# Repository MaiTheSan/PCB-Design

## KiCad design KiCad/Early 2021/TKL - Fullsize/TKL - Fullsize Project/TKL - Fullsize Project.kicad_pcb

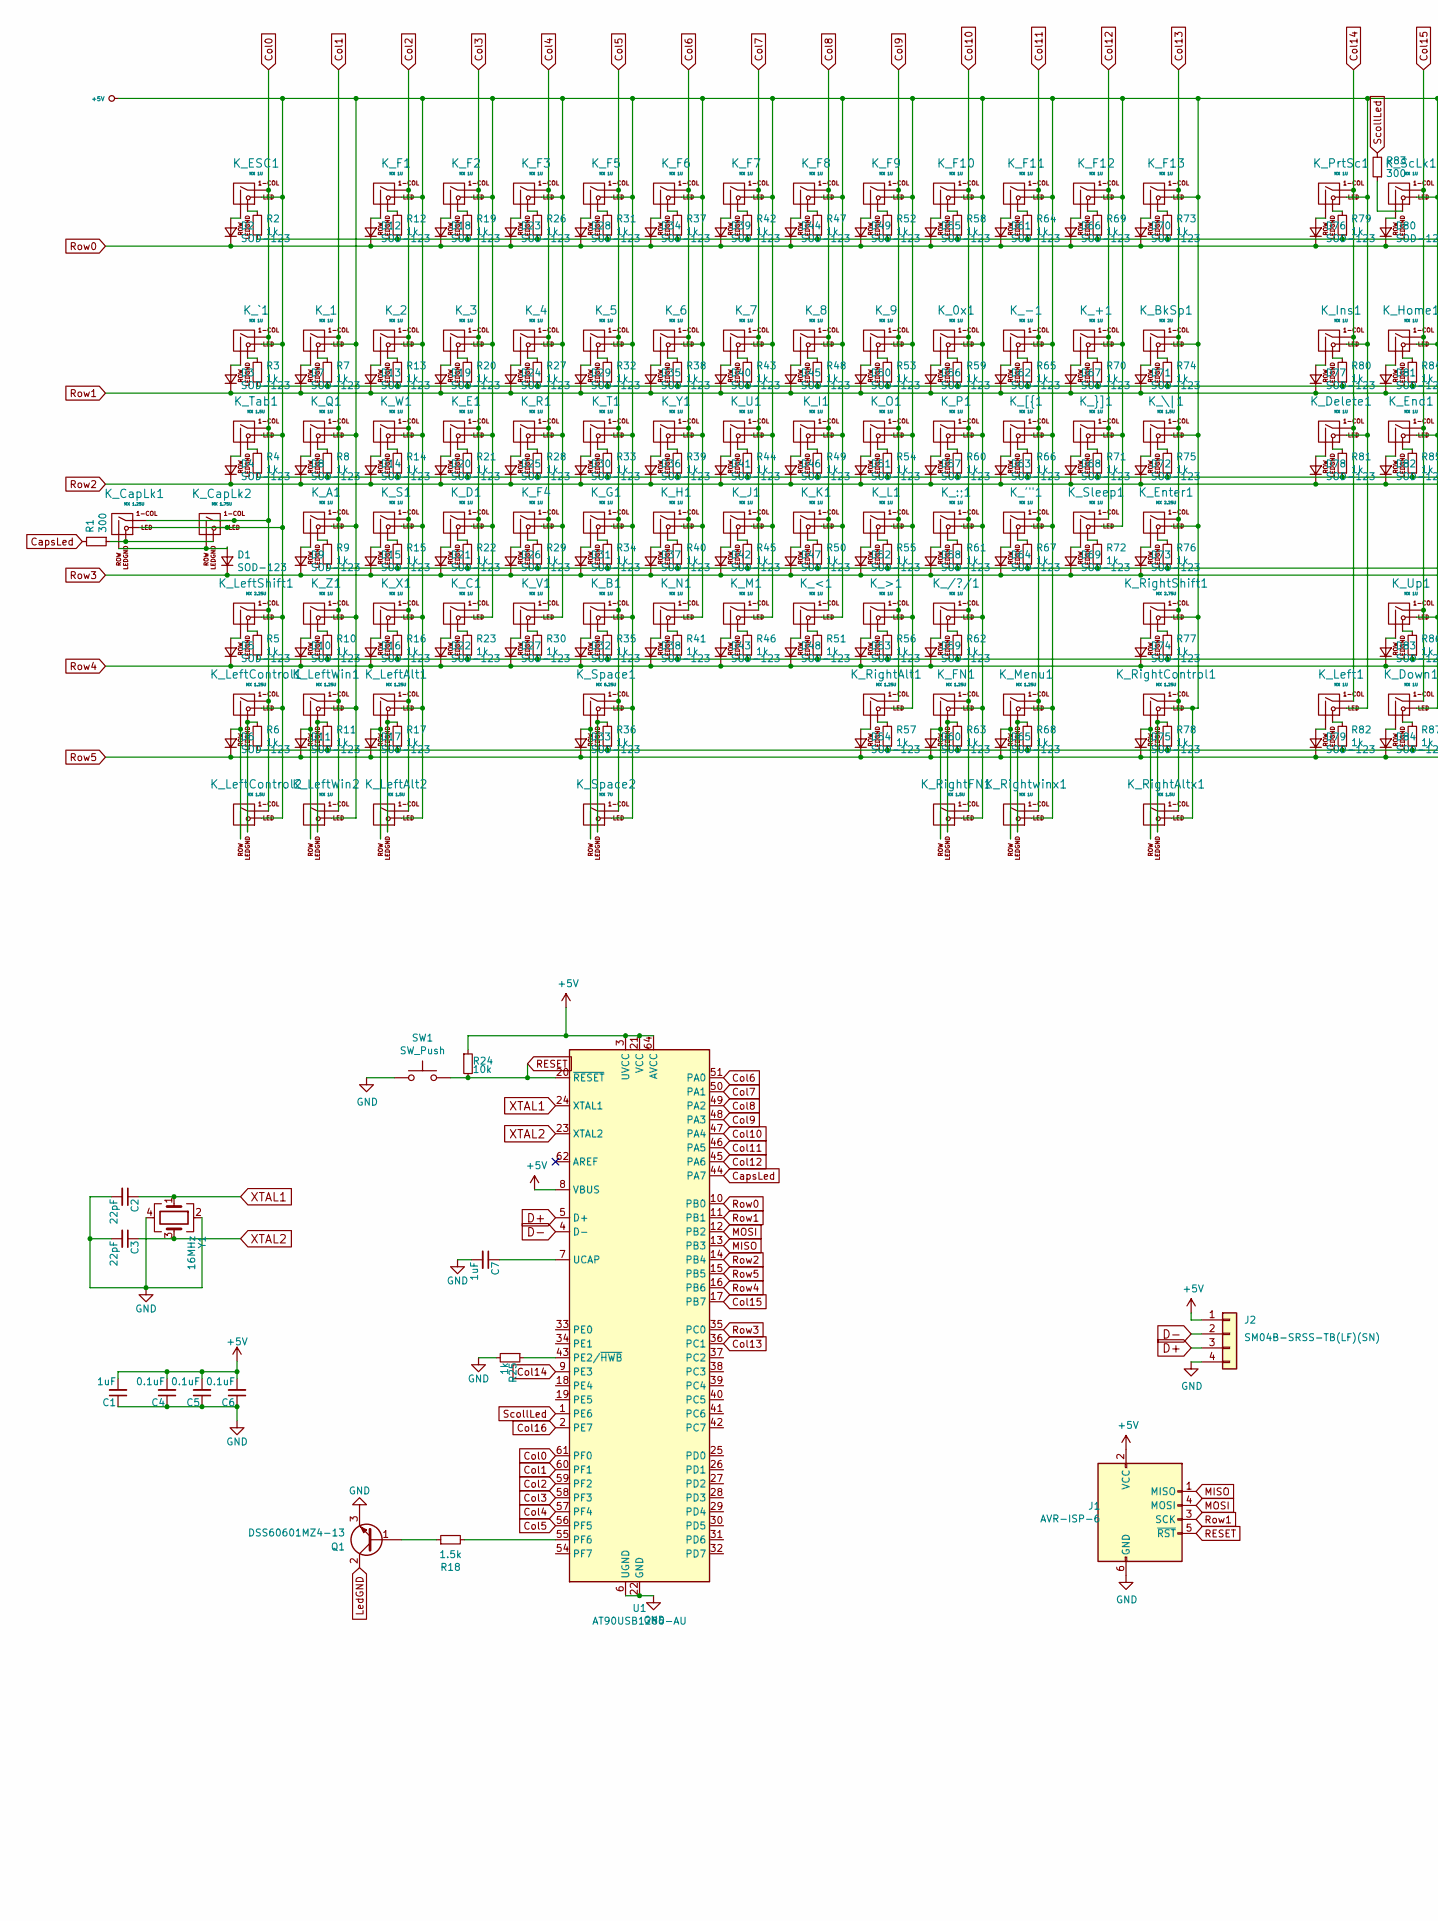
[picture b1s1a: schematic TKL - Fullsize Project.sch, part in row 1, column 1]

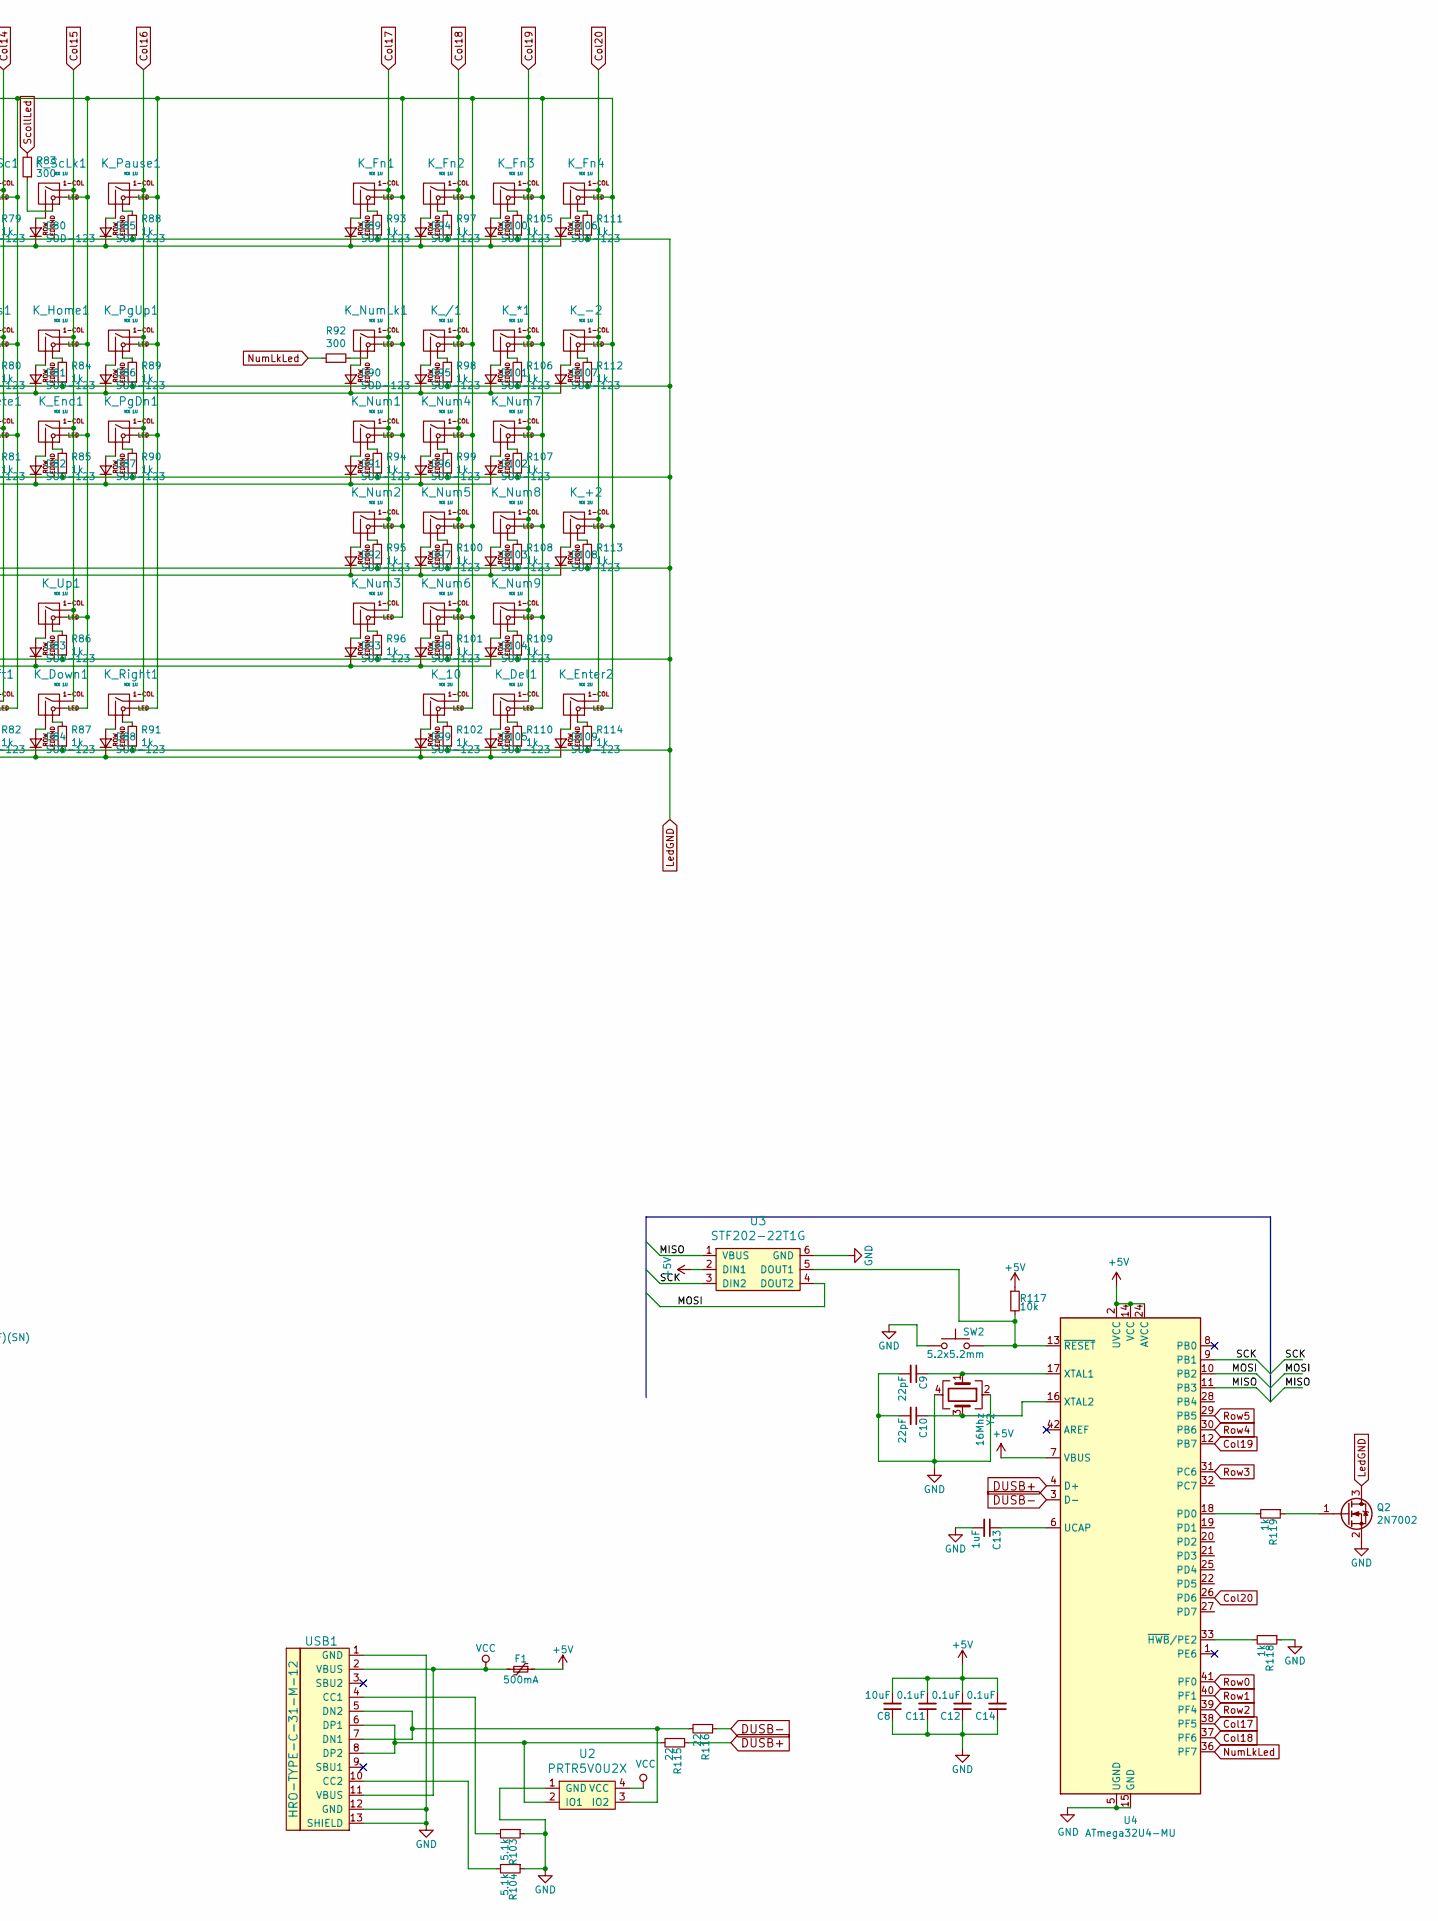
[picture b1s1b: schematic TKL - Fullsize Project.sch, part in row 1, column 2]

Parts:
C1, C7, C13: 1uF; C_0603
C2, C3, C9, C10: 22pF; C_0603
C4, C5, C6, C11, C12, C14: 0.1uF; C_0603
C8: 10uF; C_0603
D1, D2, D3, D4, D5, D6, D7, D8, D9, D10, D11, D12, D13, D14, D15, D16, D17, D18, D19, D20, D21, D22, D23, D24, D25, D26, D27, D28, D29, D30, D31, D32, D33, D34, D35, D36, D37, D38, D39, D40, D41, D42, D43, D44, D45, D46, D47, D48, D49, D50, D51, D52, D53, D54, D55, D56, D57, D58, D59, D60, D61, D62, D63, D64, D65, D66, D67, D68, D69, D70, D71, D72, D73, D74, D75, D76, D77, D78, D79, D80, D81, D82, D83, D84, D85, D86, D87, D88, D89, D90, D91, D92, D93, D94, D95, D96, D97, D98, D99, D100, D101, D102, D103, D104, D105, D106, D107, D108, D109: SOD-123; D_SOD-123-Pretty
F1: 500mA; Fuse_SMD1206_Reflow
J1: AVR-ISP-6; Reset_Pretty-Mask
J2: SM04B-SRSS-TB(LF)(SN); JST-SR-4; Manufacturer Part No SM04B-SRSS-TB(LF)(SN); LCSC Part No C160404
K_0x1, K_1, K_2, K_3, K_4, K_5, K_6, K_7, K_8, K_9: MX 1U; MXOnly-1U
K_10: MX 2U; MXOnly-2U-FLIPPED
K_'"1: MX 1U; MXOnly-1U
K_*1: MX 1U; MXOnly-1U
K_+1: MX 1U; MXOnly-1U
K_+2: MX 2U; MXOnly-2U
K_-1, K_-2: MX 1U; MXOnly-1U
K_/1: MX 1U; MXOnly-1U
K_/?/1: MX 1U; MXOnly-1U
K_:;1: MX 1U; MXOnly-1U
K_<1: MX 1U; MXOnly-1U
K_>1: MX 1U; MXOnly-1U
K_A1: MX 1U; MXOnly-1U
K_B1: MX 1U; MXOnly-1U
K_BkSp1: MX 2U; MXOnly-2U-ReversedStabilizers
K_C1: MX 1U; MXOnly-1U
K_CapLk1: MX 1.25U; MXOnly-1.25U
K_CapLk2: MX 1.75U; MXOnly-1.75U-FLIPPED
K_D1: MX 1U; MXOnly-1U
K_Del1: MX 1U; MXOnly-1U-FLIPPED
K_Delete1: MX 1U; MXOnly-1U
K_Down1: MX 1U; MXOnly-1U
K_E1: MX 1U; MXOnly-1U
K_ESC1: MX 1U; MXOnly-1U
K_End1: MX 1U; MXOnly-1U
K_Enter1: MX 2.25U; MXOnly-2.25U
K_Enter2: MX 2U; MXOnly-2U
K_F1, K_F2, K_F3, K_F4, K_F5, K_F6, K_F7, K_F8, K_F9, K_F10, K_F11, K_F12, K_F13: MX 1U; MXOnly-1U
K_FN1: MX 1.25U; MXOnly-1.25U-FLIPPED
K_Fn1, K_Fn3: MX 1U; MXOnly-1U-FLIPPED
K_Fn2, K_Fn4: MX 1U; MXOnly-1U
K_G1: MX 1U; MXOnly-1U
K_H1: MX 1U; MXOnly-1U
K_Home1: MX 1U; MXOnly-1U
K_I1: MX 1U; MXOnly-1U
K_Ins1: MX 1U; MXOnly-1U
K_J1: MX 1U; MXOnly-1U
K_K1: MX 1U; MXOnly-1U
K_L1: MX 1U; MXOnly-1U
K_Left1: MX 1U; MXOnly-1U
K_LeftAlt1: MX 1.25U; MXOnly-1.25U
K_LeftAlt2: MX 1.5U; MXOnly-1.5U-FLIPPED
K_LeftControl1: MX 1.25U; MXOnly-1.25U
K_LeftControl2: MX 1.5U; MXOnly-1.5U-FLIPPED
K_LeftShift1: MX 2.25U; MXOnly-2.25U
K_LeftWin1: MX 1.25U; MXOnly-1.25U
K_LeftWin2: MX 1U; MXOnly-1U-FLIPPED
K_M1: MX 1U; MXOnly-1U
K_Menu1: MX 1.25U; MXOnly-1.25U-FLIPPED
K_N1: MX 1U; MXOnly-1U
K_Num1, K_Num2, K_Num3, K_Num7, K_Num8, K_Num9: MX 1U; MXOnly-1U-FLIPPED
K_Num4, K_Num5, K_Num6: MX 1U; MXOnly-1U
K_NumLk1: MX 1U; MXOnly-1U-FLIPPED
K_O1: MX 1U; MXOnly-1U
K_P1: MX 1U; MXOnly-1U
K_Pause1: MX 1U; MXOnly-1U
K_PgDn1: MX 1U; MXOnly-1U
K_PgUp1: MX 1U; MXOnly-1U
K_PrtSc1: MX 1U; MXOnly-1U
K_Q1: MX 1U; MXOnly-1U
K_R1: MX 1U; MXOnly-1U
K_Right1: MX 1U; MXOnly-1U
K_RightAlt1: MX 1.25U; MXOnly-1.25U
K_RightAltx1: MX 1.5U; MXOnly-1.5U
K_RightControl1: MX 1.25U; MXOnly-1.25U-FLIPPED
K_RightFN1: MX 1.5U; MXOnly-1.5U
K_RightShift1: MX 2.75U; MXOnly-2.75U
K_Rightwinx1: MX 1U; MXOnly-1U
K_S1: MX 1U; MXOnly-1U
K_ScLk1: MX 1U; MXOnly-1U
K_Sleep1: MX 1U; MXOnly-1U
K_Space1: MX 6.25U; MXOnly-6.25U-FLIPPED
K_Space2: MX 7U; MXOnly-7U
K_T1: MX 1U; MXOnly-1U
K_Tab1: MX 1.5U; MXOnly-1.5U
K_U1: MX 1U; MXOnly-1U
K_Up1: MX 1U; MXOnly-1U
K_V1: MX 1U; MXOnly-1U
K_W1: MX 1U; MXOnly-1U
K_X1: MX 1U; MXOnly-1U
K_Y1: MX 1U; MXOnly-1U
K_Z1: MX 1U; MXOnly-1U
K_[{1: MX 1U; MXOnly-1U
K_\|1: MX 1.5U; MXOnly-1.5U
K_`1: MX 1U; MXOnly-1U
K_}]1: MX 1U; MXOnly-1U
Q1: DSS60601MZ4-13; SOT-223-3_TabPin2
Q2: 2N7002; SOT-23
R1, R83, R92: 300; R_0805
R2, R3, R4, R5, R6, R7, R8, R9, R10, R11, R12, R13, R14, R15, R16, R17, R19, R20, R21, R22, R23, R25, R26, R27, R28, R29, R30, R31, R32, R33, R34, R35, R36, R37, R38, R39, R40, R41, R42, R43, R44, R45, R46, R47, R48, R49, R50, R51, R52, R53, R54, R55, R56, R57, R58, R59, R60, R61, R62, R63, R64, R65, R66, R67, R68, R69, R70, R71, R72, R73, R74, R75, R76, R77, R78, R79, R80, R81, R82, R84, R85, R86, R87, R88, R89, R90, R91, R93, R94, R95, R96, R97, R98, R99, R100, R101, R102, R105, R106, R107, R108, R109, R110, R111, R112, R113, R114, R118, R119: 1k; R_0805
R18: 1.5k; R_0805
R24, R117: 10k; R_0805
R103, R104: 5.1k; R_0805
R115, R116: 22; R_0805
SW1: SW_Push; SKQG-1155865
SW2: 5.2x5.2mm; SKQG-1155865
U1: AT90USB1286-AU; TQFP-64_14x14mm_P0.8mm
U2: PRTR5V0U2X; SOT143B
U3: STF202-22T1G; Reset_Pretty-Mask
U4: ATmega32U4-MU; QFN-44-1EP_7x7mm_P0.5mm_EP5.2x5.2mm
USB1: HRO-TYPE-C-31-M-12; HRO-TYPE-C-31-M-12-Assembly
Y1: 16MHz; Crystal_SMD_3225-4Pin_3.2x2.5mm
Y2: 16Mhz; Crystal_SMD_3225-4Pin_3.2x2.5mm

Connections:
+5V: C1.2, C4.2, C5.2, C6.2, C8.2, C11.2, C12.2, C14.2, F1.1, J1.2 (VCC), J2.1, K_0x1.3 (LED), K_1.3 (LED), K_2.3 (LED), K_3.3 (LED), K_4.3 (LED), K_5.3 (LED), K_6.3 (LED), K_7.3 (LED), K_8.3 (LED), K_9.3 (LED), K_10.3 (LED), K_'"1.3 (LED), K_*1.3 (LED), K_+1.3 (LED), K_+2.3 (LED), K_-1.3 (LED), K_-2.3 (LED), K_/1.3 (LED), K_/?/1.3 (LED), K_:;1.3 (LED), K_<1.3 (LED), K_>1.3 (LED), K_A1.3 (LED), K_B1.3 (LED), K_BkSp1.3 (LED), K_C1.3 (LED), K_CapLk1.3 (LED), K_CapLk2.3 (LED), K_D1.3 (LED), K_Del1.3 (LED), K_Delete1.3 (LED), K_Down1.3 (LED), K_E1.3 (LED), K_ESC1.3 (LED), K_End1.3 (LED), K_Enter1.3 (LED), K_Enter2.3 (LED), K_F1.3 (LED), K_F2.3 (LED), K_F3.3 (LED), K_F4.3 (LED), K_F5.3 (LED), K_F6.3 (LED), K_F7.3 (LED), K_F8.3 (LED), K_F9.3 (LED), K_F10.3 (LED), K_F11.3 (LED), K_F12.3 (LED), K_F13.3 (LED), K_FN1.3 (LED), K_Fn1.3 (LED), K_Fn2.3 (LED), K_Fn3.3 (LED), K_Fn4.3 (LED), K_G1.3 (LED), K_H1.3 (LED), K_Home1.3 (LED), K_I1.3 (LED), K_Ins1.3 (LED), K_J1.3 (LED), K_K1.3 (LED), K_L1.3 (LED), K_Left1.3 (LED), K_LeftAlt1.3 (LED), K_LeftAlt2.3 (LED), K_LeftControl1.3 (LED), K_LeftControl2.3 (LED), K_LeftShift1.3 (LED), K_LeftWin1.3 (LED), K_LeftWin2.3 (LED), K_M1.3 (LED), K_Menu1.3 (LED), K_N1.3 (LED), K_Num1.3 (LED), K_Num2.3 (LED), K_Num3.3 (LED), K_Num4.3 (LED), K_Num5.3 (LED), K_Num6.3 (LED), K_Num7.3 (LED), K_Num8.3 (LED), K_Num9.3 (LED), K_NumLk1.3 (LED), K_O1.3 (LED), K_P1.3 (LED), K_Pause1.3 (LED), K_PgDn1.3 (LED), K_PgUp1.3 (LED), K_PrtSc1.3 (LED), K_Q1.3 (LED), K_R1.3 (LED), K_Right1.3 (LED), K_RightAlt1.3 (LED), K_RightAltx1.3 (LED), K_RightControl1.3 (LED), K_RightFN1.3 (LED), K_RightShift1.3 (LED), K_Rightwinx1.3 (LED), K_S1.3 (LED), K_ScLk1.3 (LED), K_Sleep1.3 (LED), K_Space1.3 (LED), K_Space2.3 (LED), K_T1.3 (LED), K_Tab1.3 (LED), K_U1.3 (LED), K_Up1.3 (LED), K_V1.3 (LED), K_W1.3 (LED), K_X1.3 (LED), K_Y1.3 (LED), K_Z1.3 (LED), K_[{1.3 (LED), K_\|1.3 (LED), K_`1.3 (LED), K_}]1.3 (LED), R24.1, R117.1, U1.3 (UVCC), U1.8 (VBUS), U1.21 (VCC), U1.52 (VCC), U1.64 (AVCC), U3.2 (DIN1), U4.2 (UVCC), U4.7 (VBUS), U4.14 (VCC), U4.24 (AVCC), U4.34 (VCC), U4.44 (AVCC)
/SCK: U3.3 (DIN2), U4.9 (PB1)
CapsLed: R1.2, U1.44 (PA7)
Col0: K_CapLk1.1 (COL), K_CapLk2.1 (COL), K_ESC1.1 (COL), K_LeftControl1.1 (COL), K_LeftControl2.1 (COL), K_LeftShift1.1 (COL), K_Tab1.1 (COL), K_`1.1 (COL), U1.61 (PF0)
Col1: K_1.1 (COL), K_A1.1 (COL), K_LeftWin1.1 (COL), K_LeftWin2.1 (COL), K_Q1.1 (COL), K_Z1.1 (COL), U1.60 (PF1)
Col2: K_2.1 (COL), K_F1.1 (COL), K_LeftAlt1.1 (COL), K_LeftAlt2.1 (COL), K_S1.1 (COL), K_W1.1 (COL), K_X1.1 (COL), U1.59 (PF2)
Col3: K_3.1 (COL), K_C1.1 (COL), K_D1.1 (COL), K_E1.1 (COL), K_F2.1 (COL), U1.58 (PF3)
Col4: K_4.1 (COL), K_F3.1 (COL), K_F4.1 (COL), K_R1.1 (COL), K_V1.1 (COL), U1.57 (PF4)
Col5: K_5.1 (COL), K_B1.1 (COL), K_F5.1 (COL), K_G1.1 (COL), K_Space1.1 (COL), K_Space2.1 (COL), K_T1.1 (COL), U1.56 (PF5)
Col6: K_6.1 (COL), K_F6.1 (COL), K_H1.1 (COL), K_N1.1 (COL), K_Y1.1 (COL), U1.51 (PA0)
Col7: K_7.1 (COL), K_F7.1 (COL), K_J1.1 (COL), K_M1.1 (COL), K_U1.1 (COL), U1.50 (PA1)
Col8: K_8.1 (COL), K_<1.1 (COL), K_F8.1 (COL), K_I1.1 (COL), K_K1.1 (COL), U1.49 (PA2)
Col9: K_9.1 (COL), K_>1.1 (COL), K_F9.1 (COL), K_L1.1 (COL), K_O1.1 (COL), K_RightAlt1.1 (COL), U1.48 (PA3)
Col10: K_0x1.1 (COL), K_/?/1.1 (COL), K_:;1.1 (COL), K_F10.1 (COL), K_FN1.1 (COL), K_P1.1 (COL), K_RightFN1.1 (COL), U1.47 (PA4)
Col11: K_'"1.1 (COL), K_-1.1 (COL), K_F11.1 (COL), K_Menu1.1 (COL), K_Rightwinx1.1 (COL), K_[{1.1 (COL), U1.46 (PA5)
Col12: K_+1.1 (COL), K_F12.1 (COL), K_Sleep1.1 (COL), K_}]1.1 (COL), U1.45 (PA6)
Col13: K_BkSp1.1 (COL), K_Enter1.1 (COL), K_F13.1 (COL), K_RightAltx1.1 (COL), K_RightControl1.1 (COL), K_RightShift1.1 (COL), K_\|1.1 (COL), U1.36 (PC1)
Col14: K_Delete1.1 (COL), K_Ins1.1 (COL), K_Left1.1 (COL), K_PrtSc1.1 (COL), U1.9 (PE3)
Col15: K_Down1.1 (COL), K_End1.1 (COL), K_Home1.1 (COL), K_ScLk1.1 (COL), K_Up1.1 (COL), U1.17 (PB7)
Col16: K_Pause1.1 (COL), K_PgDn1.1 (COL), K_PgUp1.1 (COL), K_Right1.1 (COL), U1.2 (PE7)
Col17: K_Fn1.1 (COL), K_Num1.1 (COL), K_Num2.1 (COL), K_Num3.1 (COL), K_NumLk1.1 (COL), U4.38 (PF5)
Col18: K_10.1 (COL), K_/1.1 (COL), K_Fn2.1 (COL), K_Num4.1 (COL), K_Num5.1 (COL), K_Num6.1 (COL), U4.37 (PF6)
Col19: K_*1.1 (COL), K_Del1.1 (COL), K_Fn3.1 (COL), K_Num7.1 (COL), K_Num8.1 (COL), K_Num9.1 (COL), U4.12 (PB7)
Col20: K_+2.1 (COL), K_-2.1 (COL), K_Enter2.1 (COL), K_Fn4.1 (COL), U4.26 (PD6)
D+: J2.3, U1.5 (D+)
D-: J2.2, U1.4 (D-)
DUSB+: R115.1, U4.4 (D+)
DUSB-: R116.1, U4.3 (D-)
GND: C1.1, C2.2, C3.2, C4.1, C5.1, C6.1, C7.2, C8.1, C9.2, C10.2, C11.1, C12.1, C13.2, C14.1, J1.6 (GND), J2.4, Q1.3 (E), Q2.2 (S), R25.2, R103.1, R104.1, R118.1, SW1.1, SW2.1, U1.6 (UGND), U1.22 (GND), U1.53 (GND), U1.63 (GND), U2.1 (GND), U3.6 (GND), U4.5 (UGND), U4.15 (GND), U4.23 (GND), U4.35 (GND), U4.43 (GND), U4.45 (GND), USB1.1 (GND), USB1.12 (GND), USB1.13 (SHIELD), Y1.2, Y1.4, Y2.2, Y2.4
LedGND: Q1.2 (C), Q2.3 (D), R2.1, R3.1, R4.1, R5.1, R6.1, R7.1, R8.1, R9.1, R10.1, R11.1, R12.1, R13.1, R14.1, R15.1, R16.1, R17.1, R19.1, R20.1, R21.1, R22.1, R23.1, R26.1, R27.1, R28.1, R29.1, R30.1, R31.1, R32.1, R33.1, R34.1, R35.1, R36.1, R37.1, R38.1, R39.1, R40.1, R41.1, R42.1, R43.1, R44.1, R45.1, R46.1, R47.1, R48.1, R49.1, R50.1, R51.1, R52.1, R53.1, R54.1, R55.1, R56.1, R57.1, R58.1, R59.1, R60.1, R61.1, R62.1, R63.1, R64.1, R65.1, R66.1, R67.1, R68.1, R69.1, R70.1, R71.1, R72.1, R73.1, R74.1, R75.1, R76.1, R77.1, R78.1, R79.1, R80.1, R81.1, R82.1, R84.1, R85.1, R86.1, R87.1, R88.1, R89.1, R90.1, R91.1, R93.1, R94.1, R95.1, R96.1, R97.1, R98.1, R99.1, R100.1, R101.1, R102.1, R105.1, R106.1, R107.1, R108.1, R109.1, R110.1, R111.1, R112.1, R113.1, R114.1
MISO: J1.1 (MISO), U1.13 (PB3), U3.1 (VBUS), U4.11 (PB3)
MOSI: J1.4 (MOSI), U1.12 (PB2), U3.4 (DOUT2), U4.10 (PB2)
unnamed: C7.1, U1.7 (UCAP)
unnamed: C9.1, U4.17 (XTAL1), Y2.1
unnamed: C10.1, U4.16 (XTAL2), Y2.3
unnamed: C13.1, U4.6 (UCAP)
unnamed: D1.2 (A), K_CapLk1.2 (ROW), K_CapLk2.2 (ROW)
unnamed: D2.2 (A), K_ESC1.2 (ROW)
unnamed: D3.2 (A), K_`1.2 (ROW)
unnamed: D4.2 (A), K_Tab1.2 (ROW)
unnamed: D5.2 (A), K_LeftShift1.2 (ROW)
unnamed: D6.2 (A), K_LeftControl1.2 (ROW), K_LeftControl2.2 (ROW)
unnamed: D7.2 (A), K_1.2 (ROW)
unnamed: D8.2 (A), K_Q1.2 (ROW)
unnamed: D9.2 (A), K_A1.2 (ROW)
unnamed: D10.2 (A), K_Z1.2 (ROW)
unnamed: D11.2 (A), K_LeftWin1.2 (ROW), K_LeftWin2.2 (ROW)
unnamed: D12.2 (A), K_F1.2 (ROW)
unnamed: D13.2 (A), K_2.2 (ROW)
unnamed: D14.2 (A), K_W1.2 (ROW)
unnamed: D15.2 (A), K_S1.2 (ROW)
unnamed: D16.2 (A), K_X1.2 (ROW)
unnamed: D17.2 (A), K_LeftAlt1.2 (ROW), K_LeftAlt2.2 (ROW)
unnamed: D18.2 (A), K_F2.2 (ROW)
unnamed: D19.2 (A), K_3.2 (ROW)
unnamed: D20.2 (A), K_E1.2 (ROW)
unnamed: D21.2 (A), K_D1.2 (ROW)
unnamed: D22.2 (A), K_C1.2 (ROW)
unnamed: D23.2 (A), K_F3.2 (ROW)
unnamed: D24.2 (A), K_4.2 (ROW)
unnamed: D25.2 (A), K_R1.2 (ROW)
unnamed: D26.2 (A), K_F4.2 (ROW)
unnamed: D27.2 (A), K_V1.2 (ROW)
unnamed: D28.2 (A), K_F5.2 (ROW)
unnamed: D29.2 (A), K_5.2 (ROW)
unnamed: D30.2 (A), K_T1.2 (ROW)
unnamed: D31.2 (A), K_G1.2 (ROW)
unnamed: D32.2 (A), K_B1.2 (ROW)
unnamed: D33.2 (A), K_Space1.2 (ROW), K_Space2.2 (ROW)
unnamed: D34.2 (A), K_F6.2 (ROW)
unnamed: D35.2 (A), K_6.2 (ROW)
unnamed: D36.2 (A), K_Y1.2 (ROW)
unnamed: D37.2 (A), K_H1.2 (ROW)
unnamed: D38.2 (A), K_N1.2 (ROW)
unnamed: D39.2 (A), K_F7.2 (ROW)
unnamed: D40.2 (A), K_7.2 (ROW)
unnamed: D41.2 (A), K_U1.2 (ROW)
unnamed: D42.2 (A), K_J1.2 (ROW)
unnamed: D43.2 (A), K_M1.2 (ROW)
unnamed: D44.2 (A), K_F8.2 (ROW)
unnamed: D45.2 (A), K_8.2 (ROW)
unnamed: D46.2 (A), K_I1.2 (ROW)
unnamed: D47.2 (A), K_K1.2 (ROW)
unnamed: D48.2 (A), K_<1.2 (ROW)
unnamed: D49.2 (A), K_F9.2 (ROW)
unnamed: D50.2 (A), K_9.2 (ROW)
unnamed: D51.2 (A), K_O1.2 (ROW)
unnamed: D52.2 (A), K_L1.2 (ROW)
unnamed: D53.2 (A), K_>1.2 (ROW)
unnamed: D54.2 (A), K_RightAlt1.2 (ROW)
unnamed: D55.2 (A), K_F10.2 (ROW)
unnamed: D56.2 (A), K_0x1.2 (ROW)
unnamed: D57.2 (A), K_P1.2 (ROW)
unnamed: D58.2 (A), K_:;1.2 (ROW)
unnamed: D59.2 (A), K_/?/1.2 (ROW)
unnamed: D60.2 (A), K_FN1.2 (ROW), K_RightFN1.2 (ROW)
unnamed: D61.2 (A), K_F11.2 (ROW)
unnamed: D62.2 (A), K_-1.2 (ROW)
unnamed: D63.2 (A), K_[{1.2 (ROW)
unnamed: D64.2 (A), K_'"1.2 (ROW)
unnamed: D65.2 (A), K_Menu1.2 (ROW), K_Rightwinx1.2 (ROW)
unnamed: D66.2 (A), K_F12.2 (ROW)
unnamed: D67.2 (A), K_+1.2 (ROW)
unnamed: D68.2 (A), K_}]1.2 (ROW)
unnamed: D69.2 (A), K_Sleep1.2 (ROW)
unnamed: D70.2 (A), K_F13.2 (ROW)
unnamed: D71.2 (A), K_BkSp1.2 (ROW)
unnamed: D72.2 (A), K_\|1.2 (ROW)
unnamed: D73.2 (A), K_Enter1.2 (ROW)
unnamed: D74.2 (A), K_RightShift1.2 (ROW)
unnamed: D75.2 (A), K_RightAltx1.2 (ROW), K_RightControl1.2 (ROW)
unnamed: D76.2 (A), K_PrtSc1.2 (ROW)
unnamed: D77.2 (A), K_Ins1.2 (ROW)
unnamed: D78.2 (A), K_Delete1.2 (ROW)
unnamed: D79.2 (A), K_Left1.2 (ROW)
unnamed: D80.2 (A), K_ScLk1.2 (ROW)
unnamed: D81.2 (A), K_Home1.2 (ROW)
unnamed: D82.2 (A), K_End1.2 (ROW)
unnamed: D83.2 (A), K_Up1.2 (ROW)
unnamed: D84.2 (A), K_Down1.2 (ROW)
unnamed: D85.2 (A), K_Pause1.2 (ROW)
unnamed: D86.2 (A), K_PgUp1.2 (ROW)
unnamed: D87.2 (A), K_PgDn1.2 (ROW)
unnamed: D88.2 (A), K_Right1.2 (ROW)
unnamed: D89.2 (A), K_Fn1.2 (ROW)
unnamed: D90.2 (A), K_NumLk1.2 (ROW)
unnamed: D91.2 (A), K_Num1.2 (ROW)
unnamed: D92.2 (A), K_Num2.2 (ROW)
unnamed: D93.2 (A), K_Num3.2 (ROW)
unnamed: D94.2 (A), K_Fn2.2 (ROW)
unnamed: D95.2 (A), K_/1.2 (ROW)
unnamed: D96.2 (A), K_Num4.2 (ROW)
unnamed: D97.2 (A), K_Num5.2 (ROW)
unnamed: D98.2 (A), K_Num6.2 (ROW)
unnamed: D99.2 (A), K_10.2 (ROW)
unnamed: D100.2 (A), K_Fn3.2 (ROW)
unnamed: D101.2 (A), K_*1.2 (ROW)
unnamed: D102.2 (A), K_Num7.2 (ROW)
unnamed: D103.2 (A), K_Num8.2 (ROW)
unnamed: D104.2 (A), K_Num9.2 (ROW)
unnamed: D105.2 (A), K_Del1.2 (ROW)
unnamed: D106.2 (A), K_Fn4.2 (ROW)
unnamed: D107.2 (A), K_-2.2 (ROW)
unnamed: D108.2 (A), K_+2.2 (ROW)
unnamed: D109.2 (A), K_Enter2.2 (ROW)
unnamed: K_0x1.4 (LEDGND), R59.2
unnamed: K_1.4 (LEDGND), R7.2
unnamed: K_2.4 (LEDGND), R13.2
unnamed: K_3.4 (LEDGND), R20.2
unnamed: K_4.4 (LEDGND), R27.2
unnamed: K_5.4 (LEDGND), R32.2
unnamed: K_6.4 (LEDGND), R38.2
unnamed: K_7.4 (LEDGND), R43.2
unnamed: K_8.4 (LEDGND), R48.2
unnamed: K_9.4 (LEDGND), R53.2
unnamed: K_10.4 (LEDGND), R102.2
unnamed: K_'"1.4 (LEDGND), R67.2
unnamed: K_*1.4 (LEDGND), R106.2
unnamed: K_+1.4 (LEDGND), R70.2
unnamed: K_+2.4 (LEDGND), R113.2
unnamed: K_-1.4 (LEDGND), R65.2
unnamed: K_-2.4 (LEDGND), R112.2
unnamed: K_/1.4 (LEDGND), R98.2
unnamed: K_/?/1.4 (LEDGND), R62.2
unnamed: K_:;1.4 (LEDGND), R61.2
unnamed: K_<1.4 (LEDGND), R51.2
unnamed: K_>1.4 (LEDGND), R56.2
unnamed: K_A1.4 (LEDGND), R9.2
unnamed: K_B1.4 (LEDGND), R35.2
unnamed: K_BkSp1.4 (LEDGND), R74.2
unnamed: K_C1.4 (LEDGND), R23.2
unnamed: K_CapLk1.4 (LEDGND), K_CapLk2.4 (LEDGND), R1.1
unnamed: K_D1.4 (LEDGND), R22.2
unnamed: K_Del1.4 (LEDGND), R110.2
unnamed: K_Delete1.4 (LEDGND), R81.2
unnamed: K_Down1.4 (LEDGND), R87.2
unnamed: K_E1.4 (LEDGND), R21.2
unnamed: K_ESC1.4 (LEDGND), R2.2
unnamed: K_End1.4 (LEDGND), R85.2
unnamed: K_Enter1.4 (LEDGND), R76.2
unnamed: K_Enter2.4 (LEDGND), R114.2
unnamed: K_F1.4 (LEDGND), R12.2
unnamed: K_F2.4 (LEDGND), R19.2
unnamed: K_F3.4 (LEDGND), R26.2
unnamed: K_F4.4 (LEDGND), R29.2
unnamed: K_F5.4 (LEDGND), R31.2
unnamed: K_F6.4 (LEDGND), R37.2
unnamed: K_F7.4 (LEDGND), R42.2
unnamed: K_F8.4 (LEDGND), R47.2
unnamed: K_F9.4 (LEDGND), R52.2
unnamed: K_F10.4 (LEDGND), R58.2
unnamed: K_F11.4 (LEDGND), R64.2
unnamed: K_F12.4 (LEDGND), R69.2
unnamed: K_F13.4 (LEDGND), R73.2
unnamed: K_FN1.4 (LEDGND), K_RightFN1.4 (LEDGND), R63.2
unnamed: K_Fn1.4 (LEDGND), R93.2
unnamed: K_Fn2.4 (LEDGND), R97.2
unnamed: K_Fn3.4 (LEDGND), R105.2
unnamed: K_Fn4.4 (LEDGND), R111.2
unnamed: K_G1.4 (LEDGND), R34.2
unnamed: K_H1.4 (LEDGND), R40.2
unnamed: K_Home1.4 (LEDGND), R84.2
unnamed: K_I1.4 (LEDGND), R49.2
unnamed: K_Ins1.4 (LEDGND), R80.2
unnamed: K_J1.4 (LEDGND), R45.2
unnamed: K_K1.4 (LEDGND), R50.2
unnamed: K_L1.4 (LEDGND), R55.2
unnamed: K_Left1.4 (LEDGND), R82.2
unnamed: K_LeftAlt1.4 (LEDGND), K_LeftAlt2.4 (LEDGND), R17.2
unnamed: K_LeftControl1.4 (LEDGND), K_LeftControl2.4 (LEDGND), R6.2
unnamed: K_LeftShift1.4 (LEDGND), R5.2
unnamed: K_LeftWin1.4 (LEDGND), K_LeftWin2.4 (LEDGND), R11.2
unnamed: K_M1.4 (LEDGND), R46.2
unnamed: K_Menu1.4 (LEDGND), K_Rightwinx1.4 (LEDGND), R68.2
unnamed: K_N1.4 (LEDGND), R41.2
unnamed: K_Num1.4 (LEDGND), R94.2
unnamed: K_Num2.4 (LEDGND), R95.2
unnamed: K_Num3.4 (LEDGND), R96.2
unnamed: K_Num4.4 (LEDGND), R99.2
unnamed: K_Num5.4 (LEDGND), R100.2
unnamed: K_Num6.4 (LEDGND), R101.2
unnamed: K_Num7.4 (LEDGND), R107.2
unnamed: K_Num8.4 (LEDGND), R108.2
unnamed: K_Num9.4 (LEDGND), R109.2
unnamed: K_NumLk1.4 (LEDGND), R92.2
unnamed: K_O1.4 (LEDGND), R54.2
unnamed: K_P1.4 (LEDGND), R60.2
unnamed: K_Pause1.4 (LEDGND), R88.2
unnamed: K_PgDn1.4 (LEDGND), R90.2
unnamed: K_PgUp1.4 (LEDGND), R89.2
unnamed: K_PrtSc1.4 (LEDGND), R79.2
unnamed: K_Q1.4 (LEDGND), R8.2
unnamed: K_R1.4 (LEDGND), R28.2
unnamed: K_Right1.4 (LEDGND), R91.2
unnamed: K_RightAlt1.4 (LEDGND), R57.2
unnamed: K_RightAltx1.4 (LEDGND), K_RightControl1.4 (LEDGND), R78.2
unnamed: K_RightShift1.4 (LEDGND), R77.2
unnamed: K_S1.4 (LEDGND), R15.2
unnamed: K_ScLk1.4 (LEDGND), R83.1
unnamed: K_Sleep1.4 (LEDGND), R72.2
unnamed: K_Space1.4 (LEDGND), K_Space2.4 (LEDGND), R36.2
unnamed: K_T1.4 (LEDGND), R33.2
unnamed: K_Tab1.4 (LEDGND), R4.2
unnamed: K_U1.4 (LEDGND), R44.2
unnamed: K_Up1.4 (LEDGND), R86.2
unnamed: K_V1.4 (LEDGND), R30.2
unnamed: K_W1.4 (LEDGND), R14.2
unnamed: K_X1.4 (LEDGND), R16.2
unnamed: K_Y1.4 (LEDGND), R39.2
unnamed: K_Z1.4 (LEDGND), R10.2
unnamed: K_[{1.4 (LEDGND), R66.2
unnamed: K_\|1.4 (LEDGND), R75.2
unnamed: K_`1.4 (LEDGND), R3.2
unnamed: K_}]1.4 (LEDGND), R71.2
unnamed: Q1.1 (B), R18.1
unnamed: Q2.1 (G), R119.1
unnamed: R18.2, U1.55 (PF6)
unnamed: R25.1, U1.43 (PE2/~HWB)
unnamed: R103.2, USB1.4 (CC1)
unnamed: R104.2, USB1.10 (CC2)
unnamed: R115.2, U2.2 (IO1), USB1.6 (DP1), USB1.8 (DP2)
unnamed: R116.2, U2.3 (IO2), USB1.5 (DN2), USB1.7 (DN1)
unnamed: R117.2, SW2.2, U3.5 (DOUT1), U4.13 (~RESET)
unnamed: R118.2, U4.33 (~HWB~/PE2)
unnamed: R119.2, U4.18 (PD0)
NumLkLed: R92.1, U4.36 (PF7)
RESET: J1.5 (~RST), R24.2, SW1.2, U1.20 (~RESET)
Row0: D2.1 (K), D12.1 (K), D18.1 (K), D23.1 (K), D28.1 (K), D34.1 (K), D39.1 (K), D44.1 (K), D49.1 (K), D55.1 (K), D61.1 (K), D66.1 (K), D70.1 (K), D76.1 (K), D80.1 (K), D85.1 (K), D89.1 (K), D94.1 (K), D100.1 (K), D106.1 (K), U1.10 (PB0), U4.41 (PF0)
Row1: D3.1 (K), D7.1 (K), D13.1 (K), D19.1 (K), D24.1 (K), D29.1 (K), D35.1 (K), D40.1 (K), D45.1 (K), D50.1 (K), D56.1 (K), D62.1 (K), D67.1 (K), D71.1 (K), D77.1 (K), D81.1 (K), D86.1 (K), D90.1 (K), D95.1 (K), D101.1 (K), D107.1 (K), J1.3 (SCK), U1.11 (PB1), U4.40 (PF1)
Row2: D4.1 (K), D8.1 (K), D14.1 (K), D20.1 (K), D25.1 (K), D30.1 (K), D36.1 (K), D41.1 (K), D46.1 (K), D51.1 (K), D57.1 (K), D63.1 (K), D68.1 (K), D72.1 (K), D78.1 (K), D82.1 (K), D87.1 (K), D91.1 (K), D96.1 (K), D102.1 (K), U1.14 (PB4), U4.39 (PF4)
Row3: D1.1 (K), D9.1 (K), D15.1 (K), D21.1 (K), D26.1 (K), D31.1 (K), D37.1 (K), D42.1 (K), D47.1 (K), D52.1 (K), D58.1 (K), D64.1 (K), D69.1 (K), D73.1 (K), D92.1 (K), D97.1 (K), D103.1 (K), D108.1 (K), U1.35 (PC0), U4.31 (PC6)
Row4: D5.1 (K), D10.1 (K), D16.1 (K), D22.1 (K), D27.1 (K), D32.1 (K), D38.1 (K), D43.1 (K), D48.1 (K), D53.1 (K), D59.1 (K), D74.1 (K), D83.1 (K), D93.1 (K), D98.1 (K), D104.1 (K), U1.16 (PB6), U4.30 (PB6)
Row5: D6.1 (K), D11.1 (K), D17.1 (K), D33.1 (K), D54.1 (K), D60.1 (K), D65.1 (K), D75.1 (K), D79.1 (K), D84.1 (K), D88.1 (K), D99.1 (K), D105.1 (K), D109.1 (K), U1.15 (PB5), U4.29 (PB5)
ScollLed: R83.2, U1.1 (PE6)
VCC: F1.2, U2.4 (VCC), USB1.2 (VBUS), USB1.11 (VBUS)
XTAL1: C2.1, U1.24 (XTAL1), Y1.1
XTAL2: C3.1, U1.23 (XTAL2), Y1.3

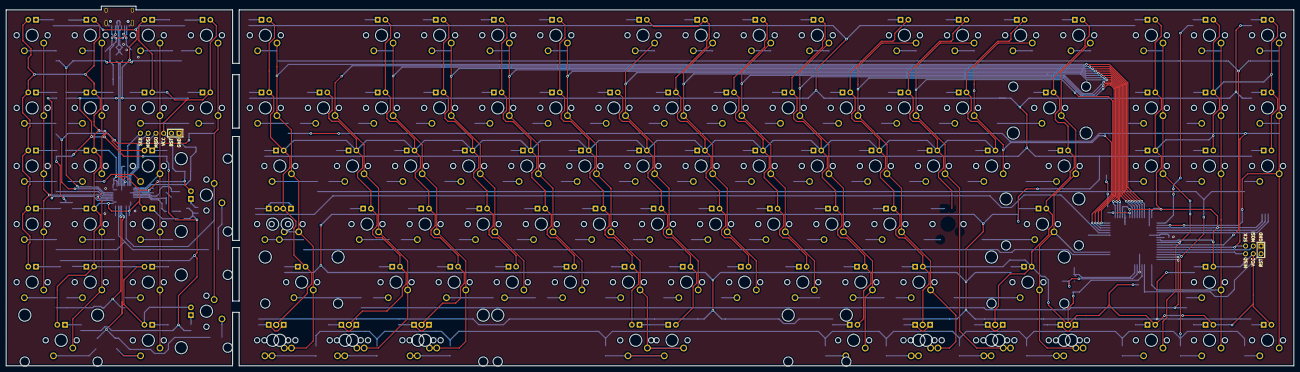
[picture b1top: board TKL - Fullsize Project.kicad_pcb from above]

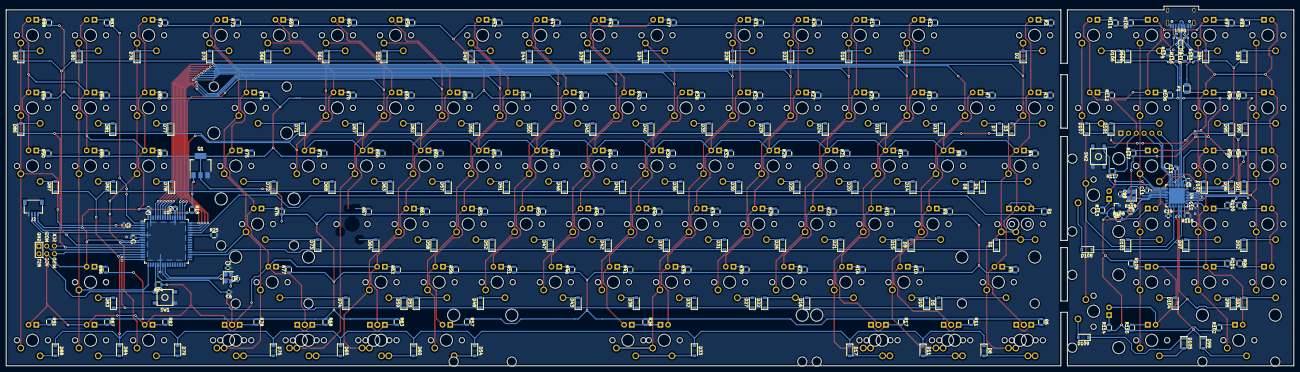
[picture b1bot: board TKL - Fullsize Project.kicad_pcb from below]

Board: 2 copper layers, 422.2 x 117.9 mm, 370 parts (252 on the bottom side), 273 nets.

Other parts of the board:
K_': MXOnly-1U

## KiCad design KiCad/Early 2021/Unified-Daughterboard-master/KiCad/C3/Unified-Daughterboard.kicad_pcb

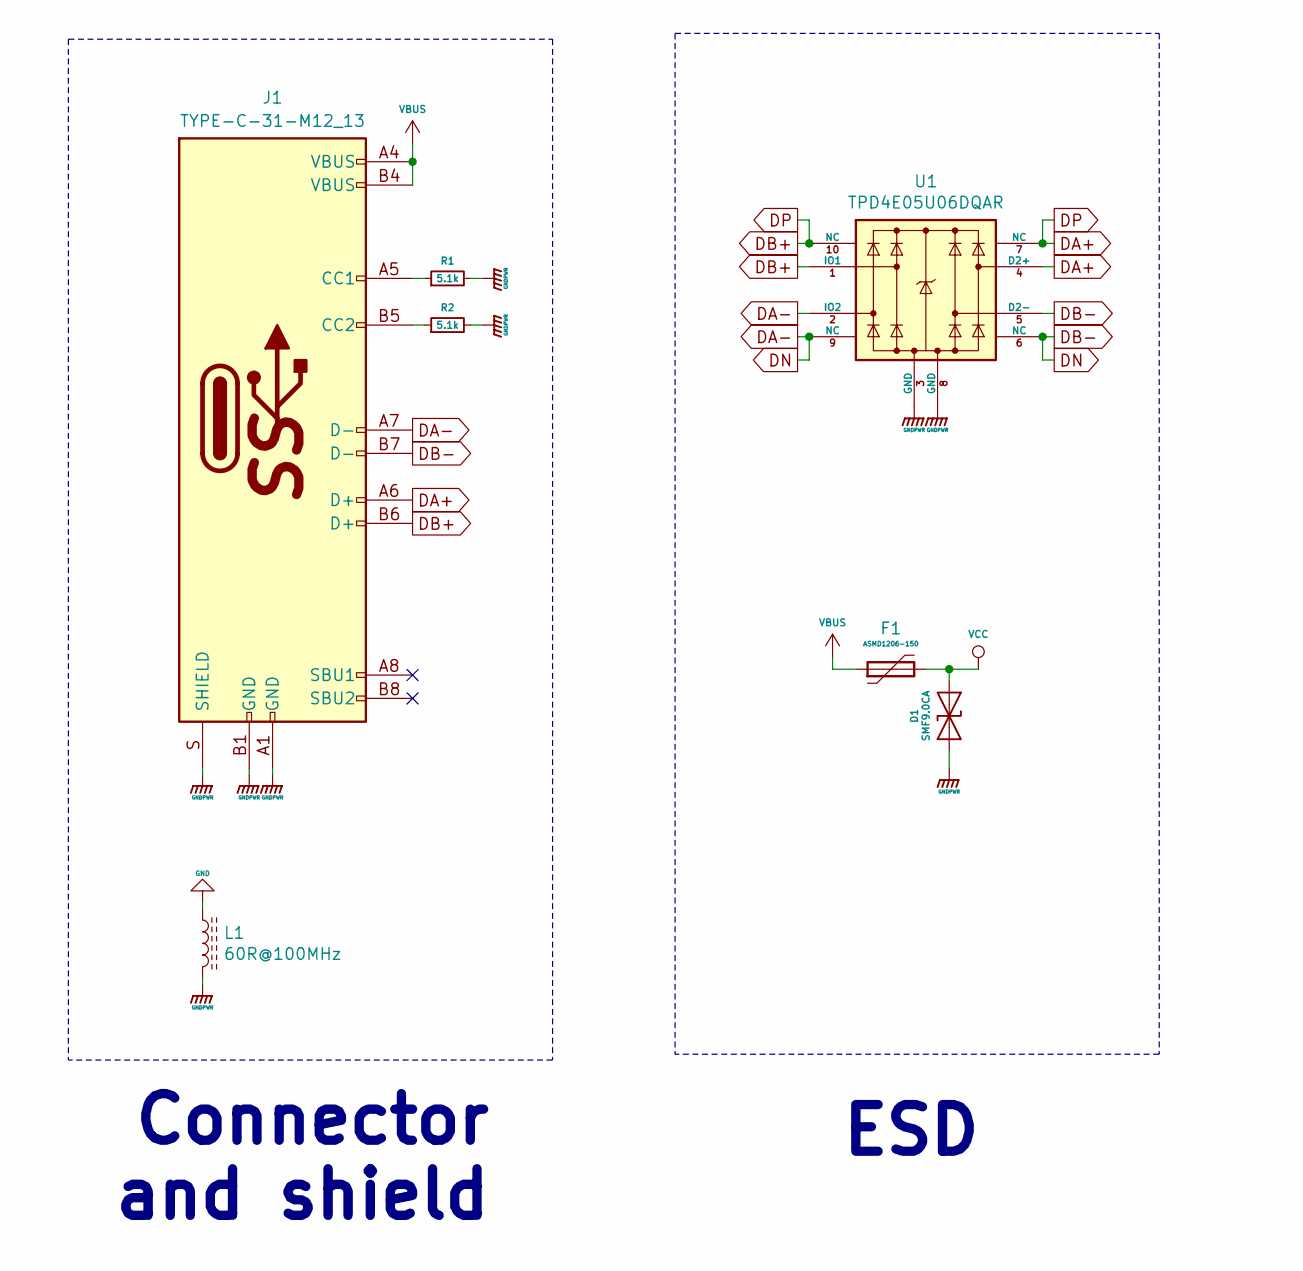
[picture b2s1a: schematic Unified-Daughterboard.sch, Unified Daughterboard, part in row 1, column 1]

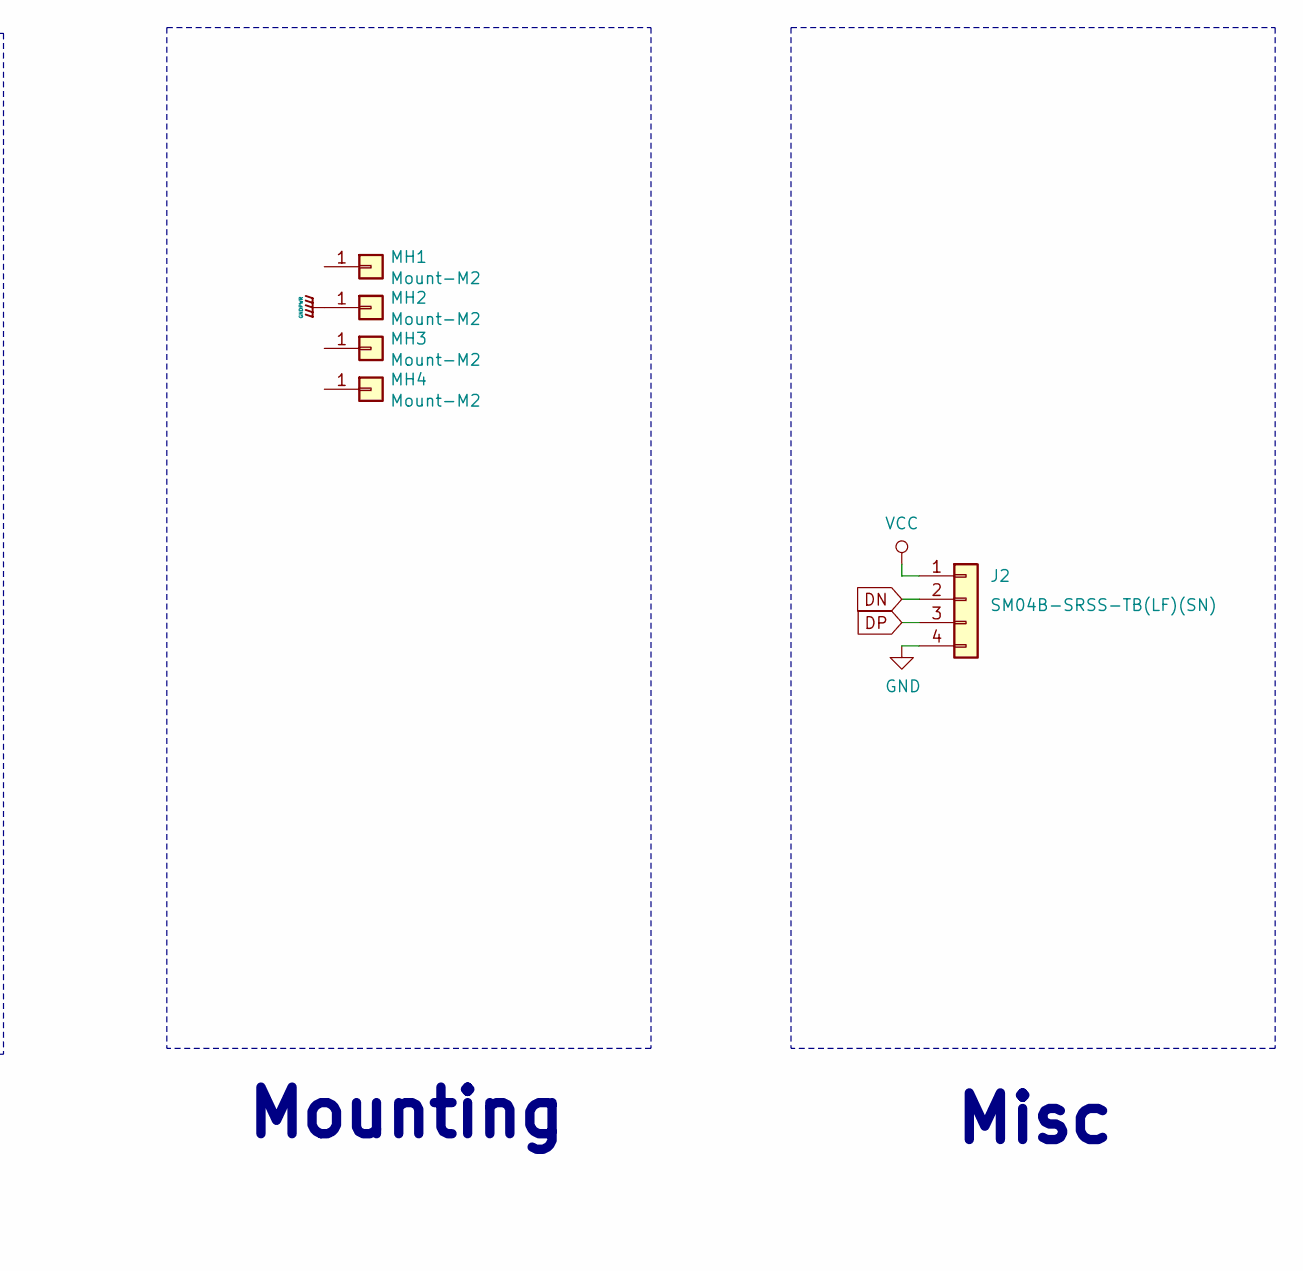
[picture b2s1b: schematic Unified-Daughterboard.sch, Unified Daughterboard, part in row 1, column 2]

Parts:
D1: SMF9.0CA; D_SOD-123_Bidirectional; Manufacturer Part No SMF9.0CA; LCSC Part No C123799
F1: ASMD1206-150; Fuse_1206_3216Metric; Manufacturer Part No ASMD1206-150; LCSC Part No C135342
J1: TYPE-C-31-M12_13; TYPE-C-31-M-12; Manufacturer Part No TYPE-C-31-M-12; LCSC Part No C165948
J2: SM04B-SRSS-TB(LF)(SN); JST-SR-4; Manufacturer Part No SM04B-SRSS-TB(LF)(SN); LCSC Part No C160404
L1: 60R@100MHz; L_1206_3216Metric; Manufacturer Part No MLB3216-600P4A(f); LCSC Part No C33600
MH1, MH2, MH3, MH4: Mount-M2; Generic-Mounthole
R1, R2: 5.1k; R_0603
U1: TPD4E05U06DQAR; USON-10_2.5x1.0mm_P0.5mm; Manufacturer Part No TPD4E05U06DQAR; LCSC Part No C138714

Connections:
DA+: J1.A6 (D+), J1.B6 (D+), J2.3, U1.1 (IO1), U1.4 (D2+), U1.7 (NC), U1.10 (NC)
DA-: J1.A7 (D-), J1.B7 (D-), J2.2, U1.2 (IO2), U1.5 (D2-), U1.6 (NC), U1.9 (NC)
GND: J2.4, L1.1
GNDPWR: D1.1 (A1), J1.A1 (GND), J1.B1 (GND), J1.S (SHIELD), L1.2, MH2.1, R1.2, R2.2, U1.3 (GND), U1.8 (GND)
unnamed: J1.A5 (CC1), R1.1
unnamed: J1.B5 (CC2), R2.1
VBUS: F1.1, J1.A4 (VBUS), J1.B4 (VBUS)
VCC: D1.2 (A2), F1.2, J2.1

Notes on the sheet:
Connector and shield
ESD
Mounting
Misc

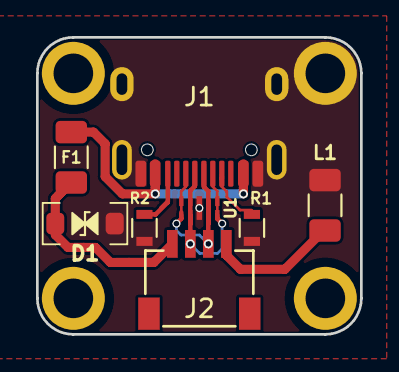
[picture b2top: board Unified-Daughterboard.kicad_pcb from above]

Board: 2 copper layers, 18.0 x 16.5 mm, 12 parts (0 on the bottom side), 8 nets.
